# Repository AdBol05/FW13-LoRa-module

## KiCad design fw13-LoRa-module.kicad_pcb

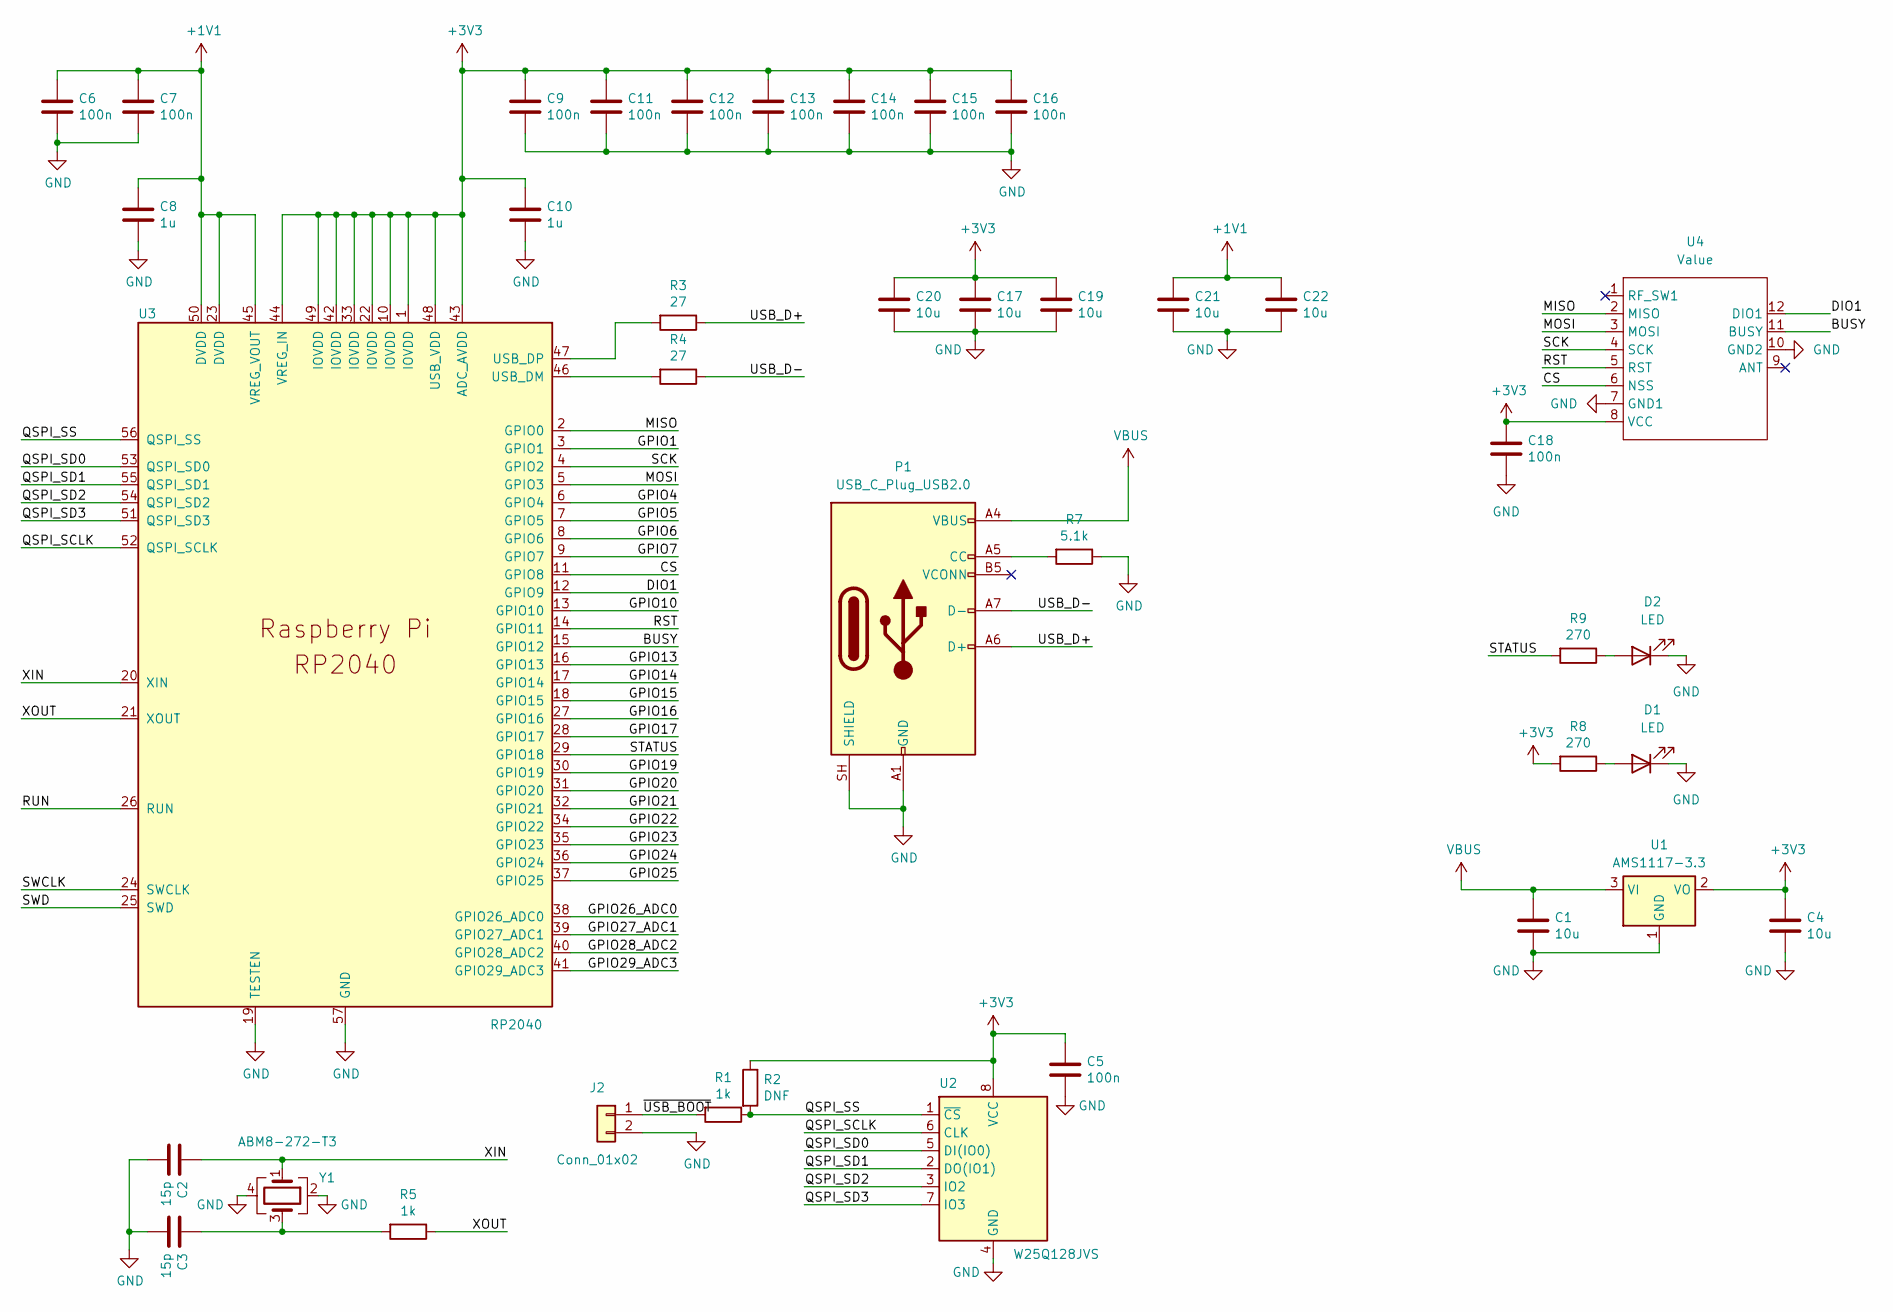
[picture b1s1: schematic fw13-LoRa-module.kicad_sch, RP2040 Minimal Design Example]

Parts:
C1, C4, C17, C19, C20, C21, C22: 10u; C_0603_1608Metric
C2, C3: 15p; C_0603_1608Metric
C5, C6, C7, C9, C11, C12, C13, C14, C15, C16, C18: 100n; C_0603_1608Metric
C8, C10: 1u; C_0603_1608Metric
D1, D2: LED; LED_0805_2012Metric
J2: Conn_01x02; PinHeader_1x02_P2.54mm_Vertical
P1: USB_C_Plug_USB2.0; USB_C_Plug_Molex_105444
R1, R5: 1k; R_0603_1608Metric
R2: DNF; R_0603_1608Metric
R3, R4: 27; R_0603_1608Metric
R7: 5.1k; R_0603_1608Metric
R8, R9: 270; R_0603_1608Metric
U1: AMS1117-3.3; SOT-223-3_TabPin2
U2: W25Q128JVS; SOIC-8_5.23x5.23mm_P1.27mm
U3: RP2040; RP2040-QFN-56
U4: Value; Wio-SX1262 PCB Package
Y1: ABM8-272-T3; Crystal_SMD_3225-4Pin_3.2x2.5mm

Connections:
+1V1: C6.1, C7.1, C8.1, C21.1, C22.1, U3.23 (DVDD), U3.45 (VREG_VOUT), U3.50 (DVDD)
+3V3: C4.1, C5.1, C9.1, C10.1, C11.1, C12.1, C13.1, C14.1, C15.1, C16.1, C17.1, C18.1, C19.1, C20.1, R2.1, R8.2, U1.2 (VO), U2.8 (VCC), U3.1 (IOVDD), U3.10 (IOVDD), U3.22 (IOVDD), U3.33 (IOVDD), U3.42 (IOVDD), U3.43 (ADC_AVDD), U3.44 (VREG_IN), U3.48 (USB_VDD), U3.49 (IOVDD), U4.8 (VCC)
/BUSY: U3.15 (GPIO12), U4.11 (BUSY)
/CS: U3.11 (GPIO8), U4.6 (NSS)
/DIO1: U3.12 (GPIO9), U4.12 (DIO1)
/GPIO1: U3.3 (GPIO1)
/GPIO4: U3.6 (GPIO4)
/GPIO5: U3.7 (GPIO5)
/GPIO6: U3.8 (GPIO6)
/GPIO7: U3.9 (GPIO7)
/GPIO10: U3.13 (GPIO10)
/GPIO13: U3.16 (GPIO13)
/GPIO14: U3.17 (GPIO14)
/GPIO15: U3.18 (GPIO15)
/GPIO16: U3.27 (GPIO16)
/GPIO17: U3.28 (GPIO17)
/GPIO19: U3.30 (GPIO19)
/GPIO20: U3.31 (GPIO20)
/GPIO21: U3.32 (GPIO21)
/GPIO22: U3.34 (GPIO22)
/GPIO23: U3.35 (GPIO23)
/GPIO24: U3.36 (GPIO24)
/GPIO25: U3.37 (GPIO25)
/GPIO26_ADC0: U3.38 (GPIO26_ADC0)
/GPIO27_ADC1: U3.39 (GPIO27_ADC1)
/GPIO28_ADC2: U3.40 (GPIO28_ADC2)
/GPIO29_ADC3: U3.41 (GPIO29_ADC3)
/MISO: U3.2 (GPIO0), U4.2 (MISO)
/MOSI: U3.5 (GPIO3), U4.3 (MOSI)
/QSPI_SCLK: U2.6 (CLK), U3.52 (QSPI_SCLK)
/QSPI_SD0: U2.5 (DI(IO0)), U3.53 (QSPI_SD0)
/QSPI_SD1: U2.2 (DO(IO1)), U3.55 (QSPI_SD1)
/QSPI_SD2: U2.3 (IO2), U3.54 (QSPI_SD2)
/QSPI_SD3: U2.7 (IO3), U3.51 (QSPI_SD3)
/QSPI_SS: R1.1, R2.2, U2.1 (~CS), U3.56 (QSPI_SS)
/RST: U3.14 (GPIO11), U4.5 (RST)
/RUN: U3.26 (RUN)
/SCK: U3.4 (GPIO2), U4.4 (SCK)
/STATUS: R9.2, U3.29 (GPIO18)
/SWCLK: U3.24 (SWCLK)
/SWD: U3.25 (SWD)
/USB_D+: P1.A6 (D+), R3.1
/USB_D-: P1.A7 (D-), R4.1
/XIN: C2.1, U3.20 (XIN), Y1.1
/XOUT: R5.1, U3.21 (XOUT)
/~USB_BOOT: J2.1, R1.2
GND: C1.2, C2.2, C3.2, C4.2, C5.2, C6.2, C7.2, C8.2, C9.2, C10.2, C11.2, C12.2, C13.2, C14.2, C15.2, C16.2, C17.2, C18.2, C19.2, C20.2, C21.2, C22.2, D1.1 (K), D2.1 (K), J2.2, P1.A1 (GND), P1.A12 (GND), P1.B1 (GND), P1.B12 (GND), P1.SH (SHIELD), R7.1, U1.1 (GND), U2.4 (GND), U3.19 (TESTEN), U3.57 (GND), U4.7 (GND1), U4.10 (GND2), Y1.2, Y1.4
unnamed: C3.1, R5.2, Y1.3
unnamed: D1.2 (A), R8.1
unnamed: D2.2 (A), R9.1
unnamed: P1.A5 (CC), R7.2
unnamed: R4.2, U3.46 (USB_DM)
unnamed: R3.2, U3.47 (USB_DP)
VBUS: C1.1, P1.A4 (VBUS), P1.A9 (VBUS), P1.B4 (VBUS), P1.B9 (VBUS), U1.3 (VI)

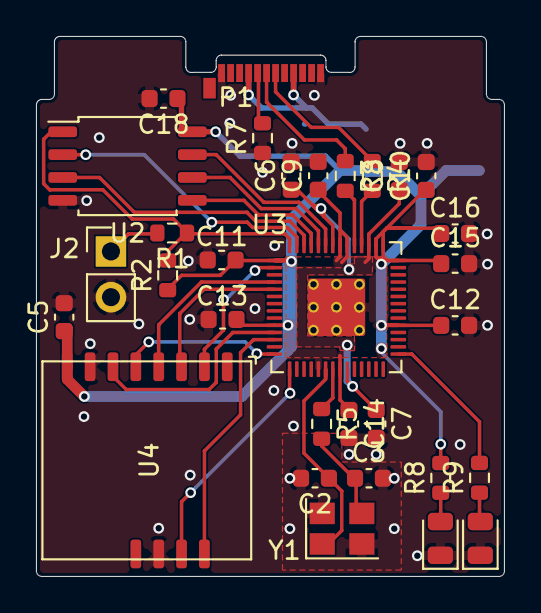
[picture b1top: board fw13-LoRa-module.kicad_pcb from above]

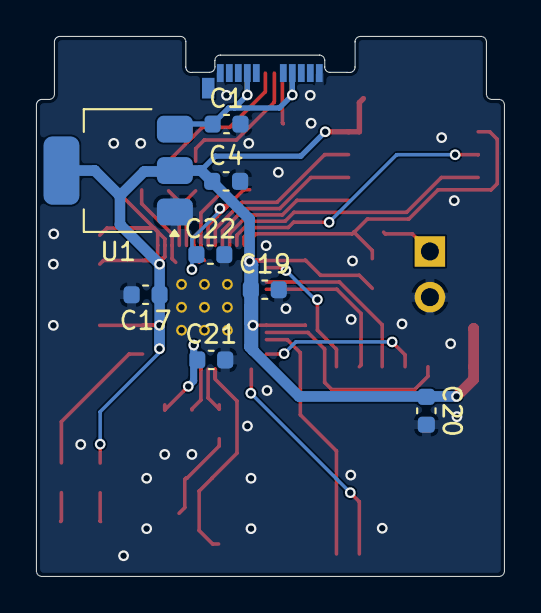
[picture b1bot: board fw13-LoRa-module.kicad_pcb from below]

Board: 2 copper layers, 26.0 x 30.0 mm, 39 parts (8 on the bottom side), 29 nets.

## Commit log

2026-05-07 init
2026-05-07 LM2675MX base
2026-05-07 USB C base
2026-05-08 AAAAAAAA
2026-05-13 trails base
2026-05-14 wiring base
2026-05-18 idfk
